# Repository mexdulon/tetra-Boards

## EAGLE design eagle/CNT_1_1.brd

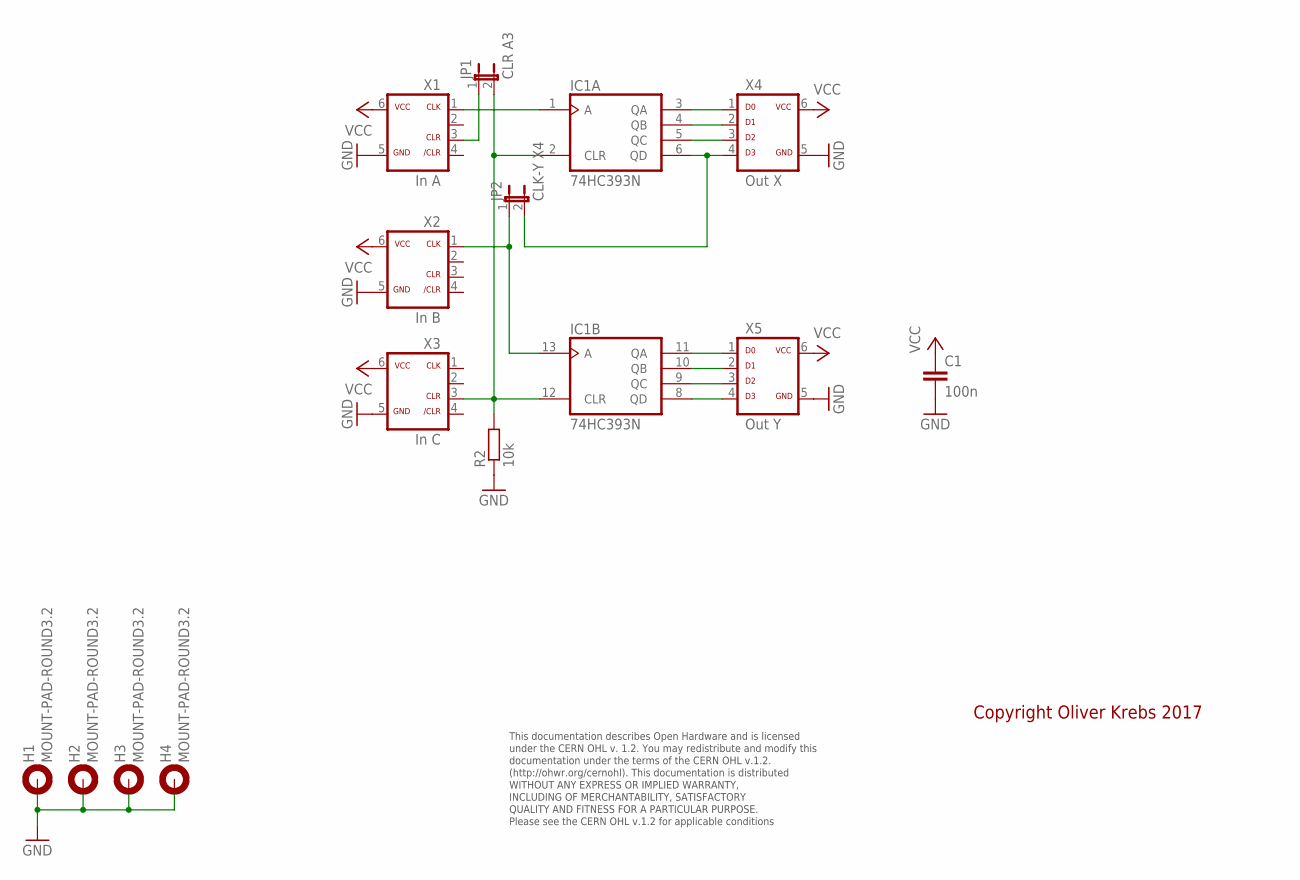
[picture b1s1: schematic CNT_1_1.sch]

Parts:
C1: 100n; C050-025X075
H1, H2, H3, H4: MOUNT-PAD-ROUND3.2; 3,2-PAD
IC1: 74HC393N; DIL14
JP1: CLR A3; JP1
JP2: CLK-Y X4; JP1
R2: 10k; 0207/10
X1: In A; ML-6
X2: In B; ML-6
X3: In C; ML-6
X4: Out X; ML-6
X5: Out Y; ML-6

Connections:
GND: C1.2, H1.B3,2, H2.B3,2, H3.B3,2, H4.B3,2, IC1.7 (GND), R2.1, X1.5, X2.5, X3.5, X4.5, X5.5
unnamed: IC1.3 (QA), X4.1
unnamed: IC1.4 (QB), X4.2
unnamed: IC1.5 (QC), X4.3
unnamed: IC1.1 (A), X1.1
unnamed: JP1.1, X1.3
unnamed: IC1.6 (QD), JP2.2, X4.4
unnamed: IC1.2 (CLR), IC1.12 (CLR), JP1.2, R2.2, X3.3
unnamed: IC1.13 (A), JP2.1, X2.1
unnamed: IC1.11 (QA), X5.1
unnamed: IC1.10 (QB), X5.2
unnamed: IC1.9 (QC), X5.3
unnamed: IC1.8 (QD), X5.4
VCC: C1.1, IC1.14 (VCC), X1.6, X2.6, X3.6, X4.6, X5.6

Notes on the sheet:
This documentation describes Open Hardware and is licensed under the CERN OHL v. 1.2. You may redistribute and modify this documentation under the terms of the CERN OHL v.1.2. (http://ohwr.org/cernohl). This documentation is distributed WITHOUT ANY EXPRESS OR IMPLIED WARRANTY, INCLUDING OF MERCHANT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
Copyright Oliver Krebs 2017

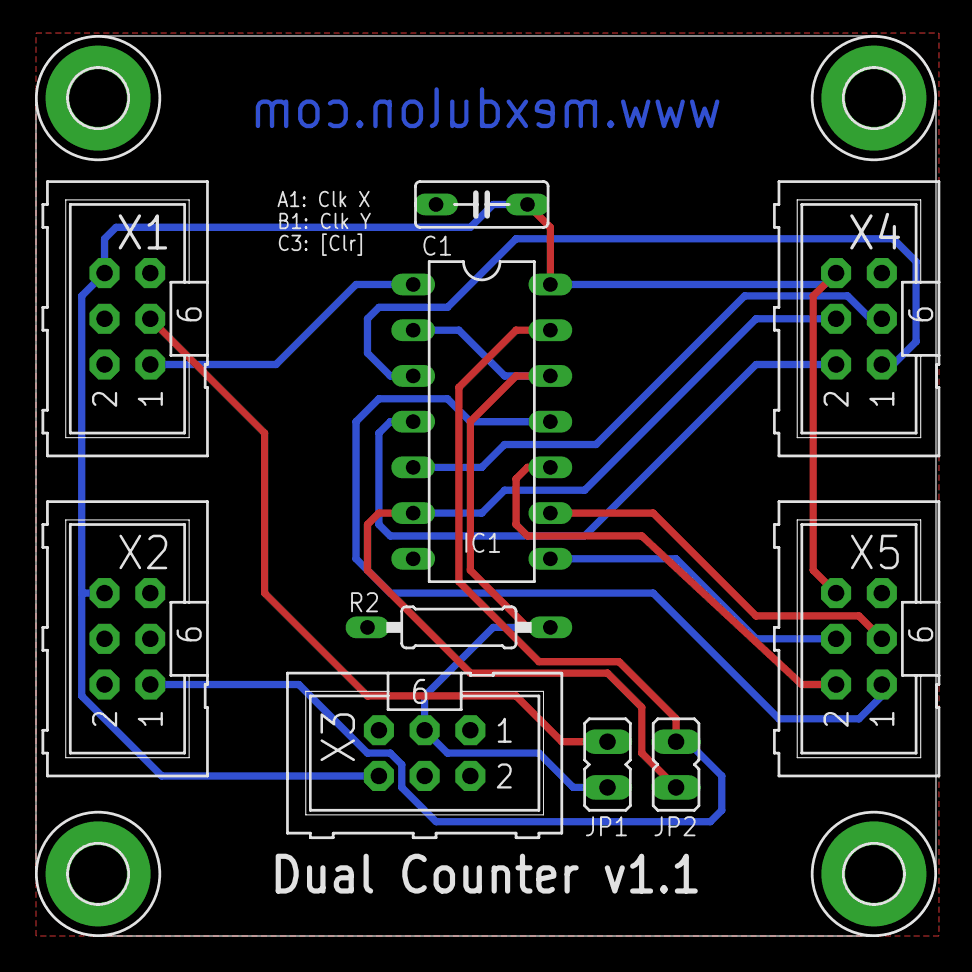
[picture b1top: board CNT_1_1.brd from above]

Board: 2 copper layers, 50.0 x 50.0 mm, 14 parts (0 on the bottom side), 14 nets.

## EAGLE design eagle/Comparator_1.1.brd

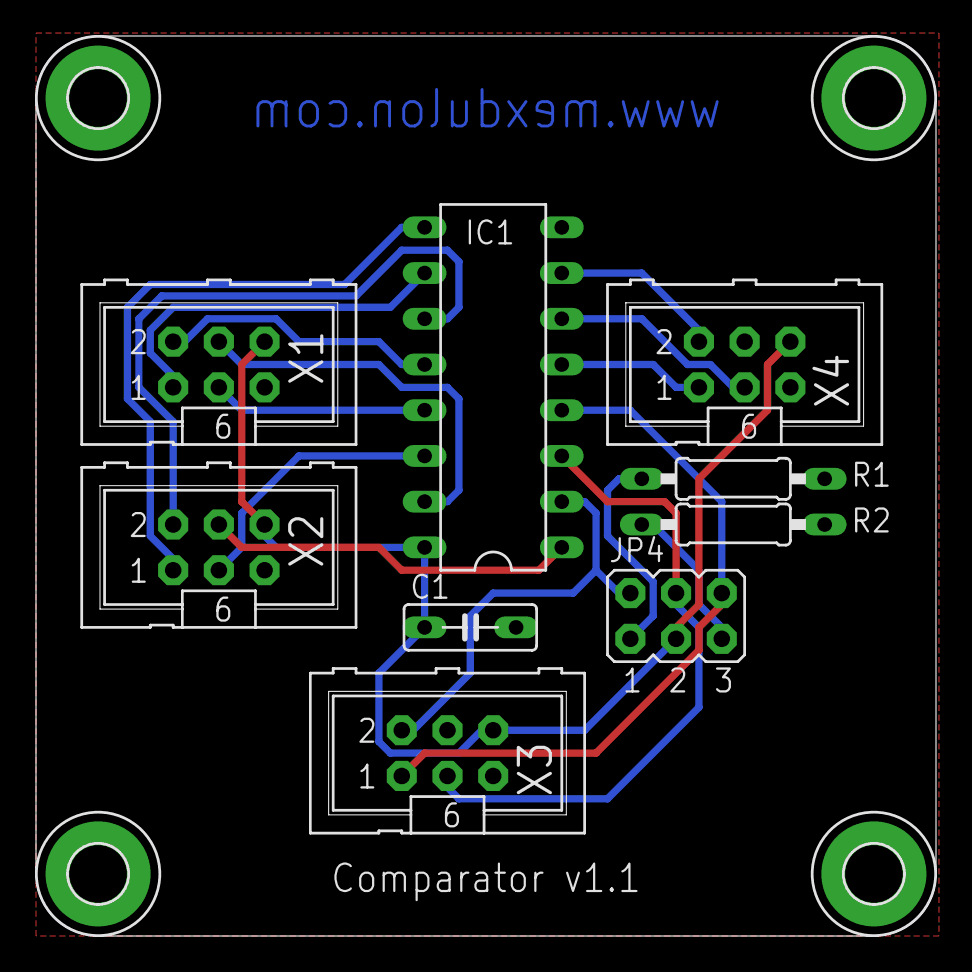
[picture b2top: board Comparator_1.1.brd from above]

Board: 2 copper layers, 50.0 x 50.0 mm, 13 parts (0 on the bottom side), 18 nets.

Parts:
C1: 100n; C050-025X075
H1, H2, H3, H4: MOUNT-PAD-ROUND3.2; 3,2-PAD
IC1: 74HC85N; DIL16
JP4: CMP STD; JP3Q
R1, R2: 10k; 0207/10
X1: In A; ML-6
X2: In B; ML-6
X3: In Cmp; ML-6
X4: Out; ML-6

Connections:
GND: C1.2, H1.B3,2, H2.B3,2, H3.B3,2, H4.B3,2, IC1.8, R1.2, R2.2, X1.5, X2.5, X3.5, X4.5
unnamed: IC1.10, X1.1
unnamed: IC1.12, X1.2
unnamed: IC1.13, X1.3
unnamed: IC1.15, X1.4
unnamed: IC1.9, X2.1
unnamed: IC1.11, X2.2
unnamed: IC1.14, X2.3
unnamed: IC1.1, X2.4
unnamed: IC1.3, JP4.4, X3.3
unnamed: IC1.2, JP4.2, X3.2
unnamed: IC1.4, JP4.6, X3.1
unnamed: IC1.5, X4.1
unnamed: IC1.7, X4.2
unnamed: IC1.6, X4.3
unnamed: JP4.1, R1.1
unnamed: JP4.5, R2.1
VCC: C1.1, IC1.16, JP4.3, X1.6, X2.6, X3.6, X4.6

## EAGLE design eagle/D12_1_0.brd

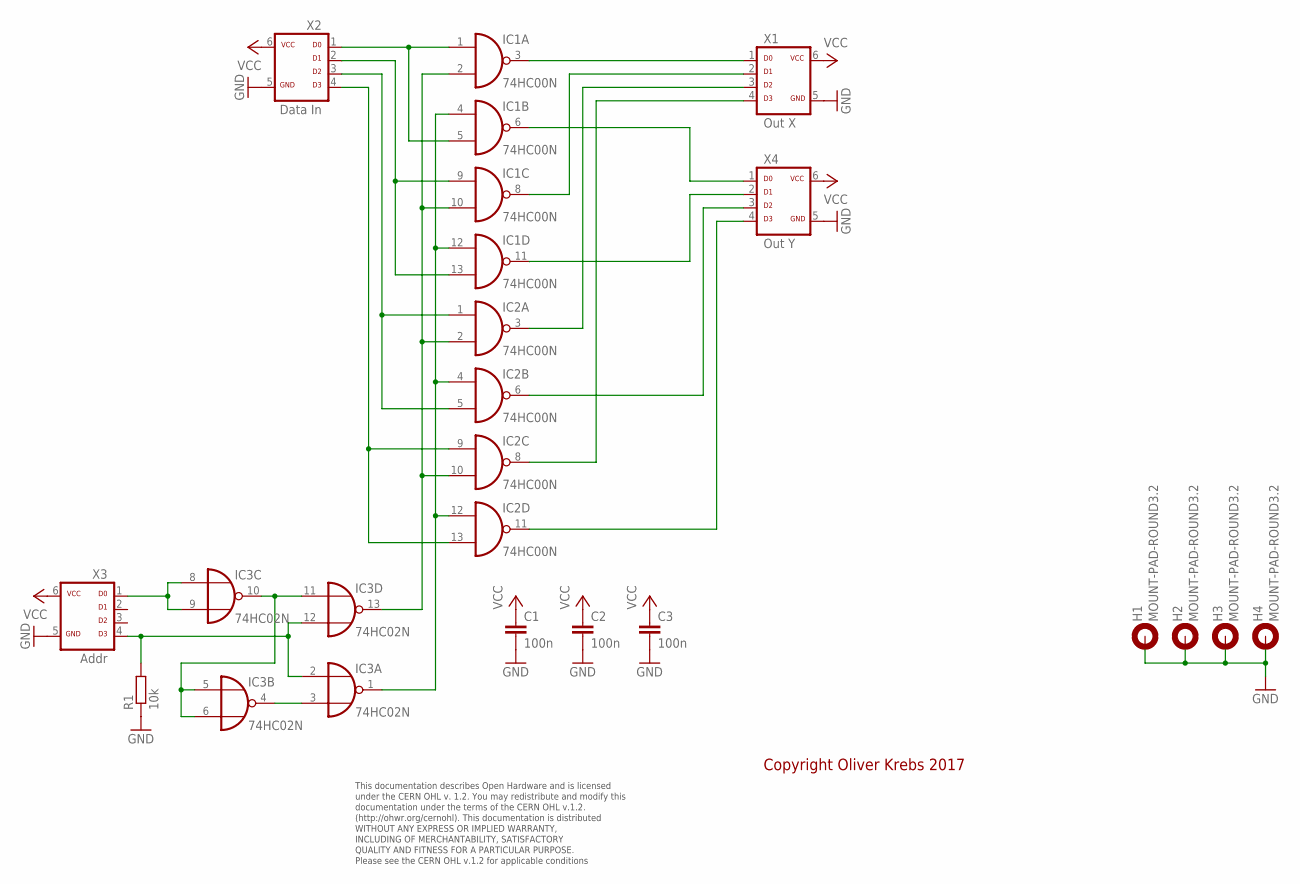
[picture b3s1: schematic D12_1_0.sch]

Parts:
C1, C2, C3: 100n; C050-025X075
H1, H2, H3, H4: MOUNT-PAD-ROUND3.2; 3,2-PAD
IC1, IC2: 74HC00N; DIL14
IC3: 74HC02N; DIL14
R1: 10k; 0207/10
X1: Out X; ML-6
X2: Data In; ML-6
X3: Addr; ML-6
X4: Out Y; ML-6

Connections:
GND: C1.2, C2.2, C3.2, H1.B3,2, H2.B3,2, H3.B3,2, H4.B3,2, IC1.7 (GND), IC2.7 (GND), IC3.7 (GND), R1.1, X1.5, X2.5, X3.5, X4.5
unnamed: IC1.3 (O), X1.1
unnamed: IC1.8 (O), X1.2
unnamed: IC2.3 (O), X1.3
unnamed: IC1.1 (I0), IC1.5 (I1), X2.1
unnamed: IC1.9 (I0), IC1.13 (I1), X2.2
unnamed: IC2.1 (I0), IC2.5 (I1), X2.3
unnamed: IC2.9 (I0), IC2.13 (I1), X2.4
unnamed: IC2.8 (O), X1.4
unnamed: IC1.6 (O), X4.1
unnamed: IC1.11 (O), X4.2
unnamed: IC2.6 (O), X4.3
unnamed: IC2.11 (O), X4.4
unnamed: IC3.5 (I0), IC3.6 (I1), IC3.10 (O), IC3.11 (I0)
unnamed: IC3.2 (I0), IC3.12 (I1), R1.2, X3.4
unnamed: IC1.2 (I1), IC1.10 (I1), IC2.2 (I1), IC2.10 (I1), IC3.13 (O)
unnamed: IC1.4 (I0), IC1.12 (I0), IC2.4 (I0), IC2.12 (I0), IC3.1 (O)
unnamed: IC3.3 (I1), IC3.4 (O)
unnamed: IC3.8 (I0), IC3.9 (I1), X3.1
VCC: C1.1, C2.1, C3.1, IC1.14 (VCC), IC2.14 (VCC), IC3.14 (VCC), X1.6, X2.6, X3.6, X4.6

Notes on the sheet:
This documentation describes Open Hardware and is licensed under the CERN OHL v. 1.2. You may redistribute and modify this documentation under the terms of the CERN OHL v.1.2. (http://ohwr.org/cernohl). This documentation is distributed WITHOUT ANY EXPRESS OR IMPLIED WARRANTY, INCLUDING OF MERCHANT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
Copyright Oliver Krebs 2017

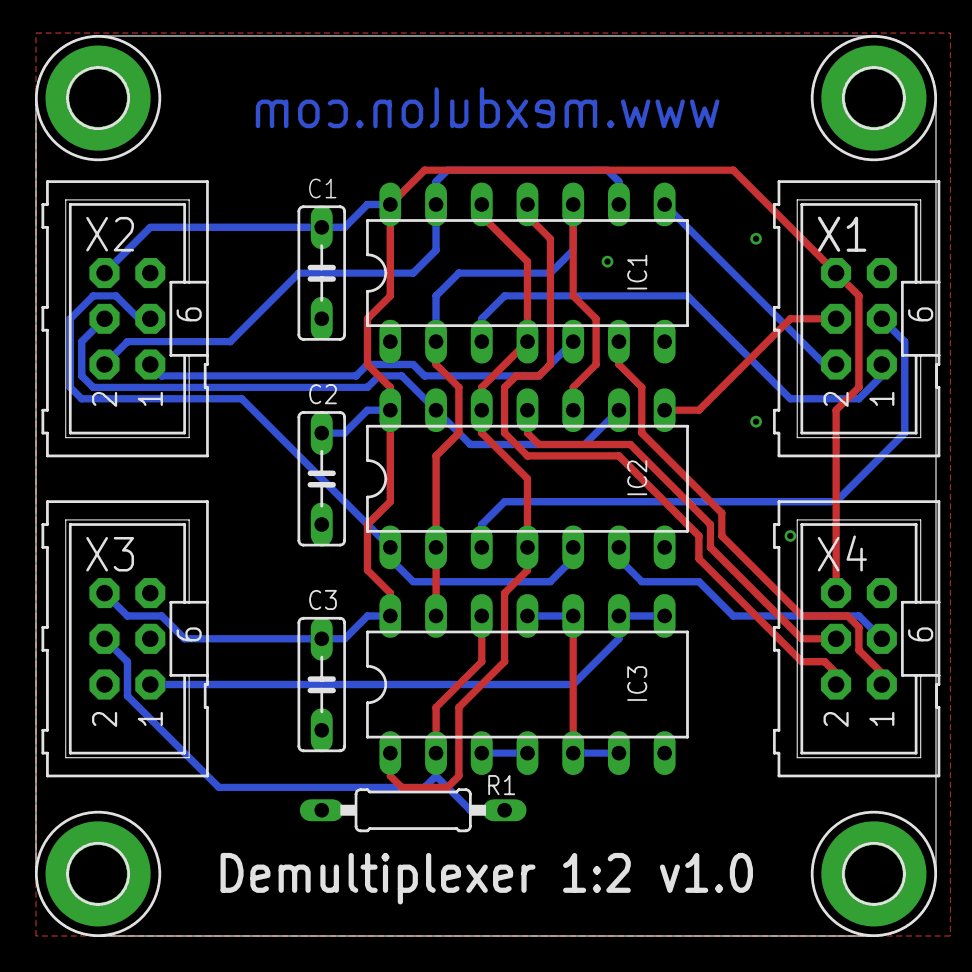
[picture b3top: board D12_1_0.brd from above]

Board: 2 copper layers, 50.0 x 50.0 mm, 15 parts (0 on the bottom side), 20 nets.

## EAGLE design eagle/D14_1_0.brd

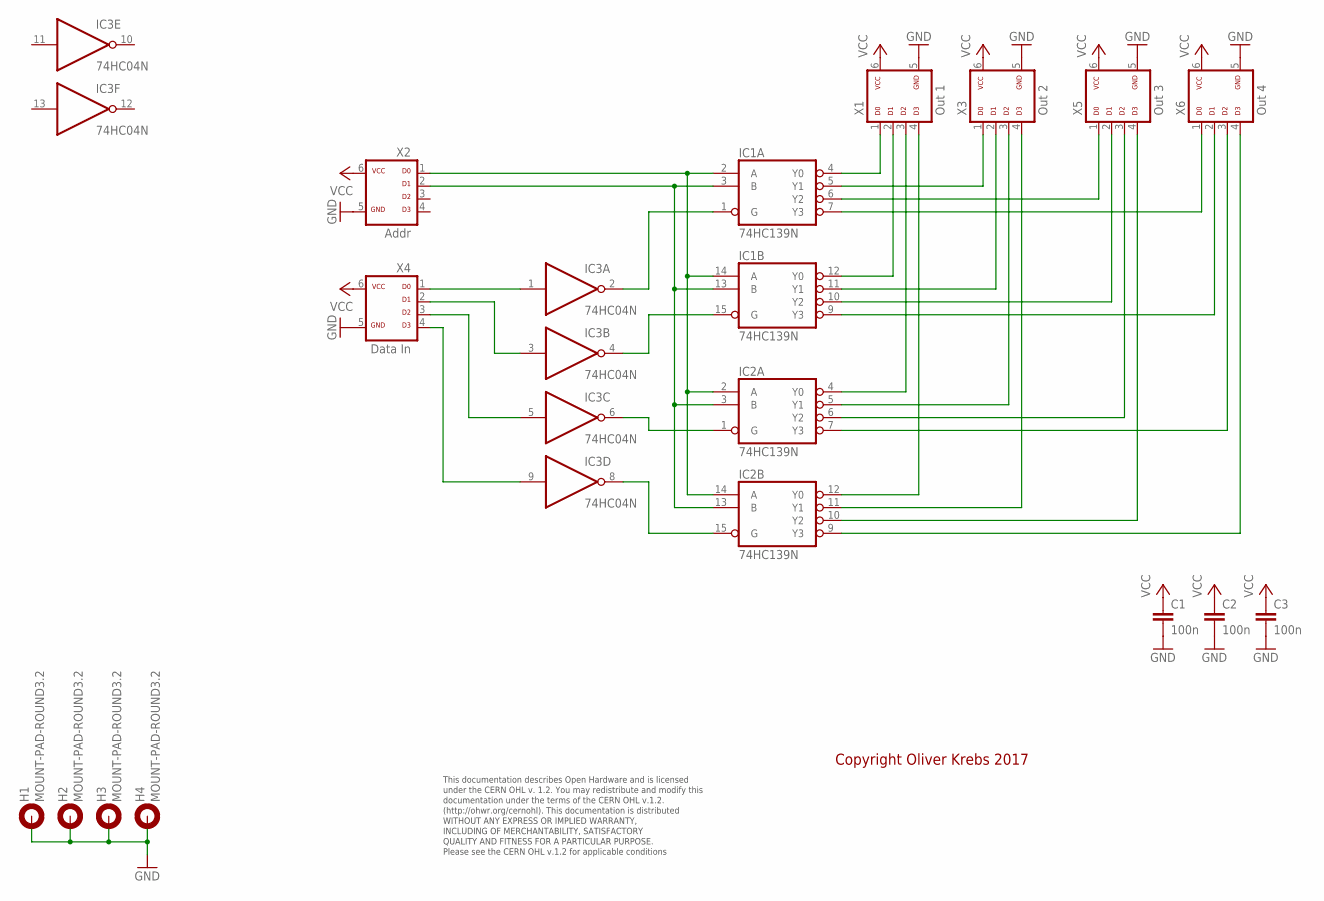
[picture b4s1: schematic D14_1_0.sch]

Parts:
C1, C2, C3: 100n; C050-025X075
H1, H2, H3, H4: MOUNT-PAD-ROUND3.2; 3,2-PAD
IC1, IC2: 74HC139N; DIL16
IC3: 74HC04N; DIL14
X1: Out 1; ML-6
X2: Addr; ML-6
X3: Out 2; ML-6
X4: Data In; ML-6
X5: Out 3; ML-6
X6: Out 4; ML-6

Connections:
GND: C1.2, C2.2, C3.2, H1.B3,2, H2.B3,2, H3.B3,2, H4.B3,2, IC1.8 (GND), IC2.8 (GND), IC3.7 (GND), X1.5, X2.5, X3.5, X4.5, X5.5, X6.5
unnamed: IC1.2 (A), IC1.14 (A), IC2.2 (A), IC2.14 (A), X2.1
unnamed: IC1.3 (B), IC1.13 (B), IC2.3 (B), IC2.13 (B), X2.2
unnamed: IC1.4 (Y0), X1.1
unnamed: IC1.12 (Y0), X1.2
unnamed: IC2.4 (Y0), X1.3
unnamed: IC2.12 (Y0), X1.4
unnamed: IC1.5 (Y1), X3.1
unnamed: IC1.11 (Y1), X3.2
unnamed: IC2.5 (Y1), X3.3
unnamed: IC2.11 (Y1), X3.4
unnamed: IC1.6 (Y2), X5.1
unnamed: IC1.10 (Y2), X5.2
unnamed: IC2.6 (Y2), X5.3
unnamed: IC2.10 (Y2), X5.4
unnamed: IC1.7 (Y3), X6.1
unnamed: IC1.9 (Y3), X6.2
unnamed: IC2.7 (Y3), X6.3
unnamed: IC2.9 (Y3), X6.4
unnamed: IC1.1 (G), IC3.2 (O)
unnamed: IC1.15 (G), IC3.4 (O)
unnamed: IC2.1 (G), IC3.6 (O)
unnamed: IC2.15 (G), IC3.8 (O)
unnamed: IC3.1 (I), X4.1
unnamed: IC3.3 (I), X4.2
unnamed: IC3.5 (I), X4.3
unnamed: IC3.9 (I), X4.4
VCC: C1.1, C2.1, C3.1, IC1.16 (VCC), IC2.16 (VCC), IC3.14 (VCC), X1.6, X2.6, X3.6, X4.6, X5.6, X6.6

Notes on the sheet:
This documentation describes Open Hardware and is licensed under the CERN OHL v. 1.2. You may redistribute and modify this documentation under the terms of the CERN OHL v.1.2. (http://ohwr.org/cernohl). This documentation is distributed WITHOUT ANY EXPRESS OR IMPLIED WARRANTY, INCLUDING OF MERCHANT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
Copyright Oliver Krebs 2017

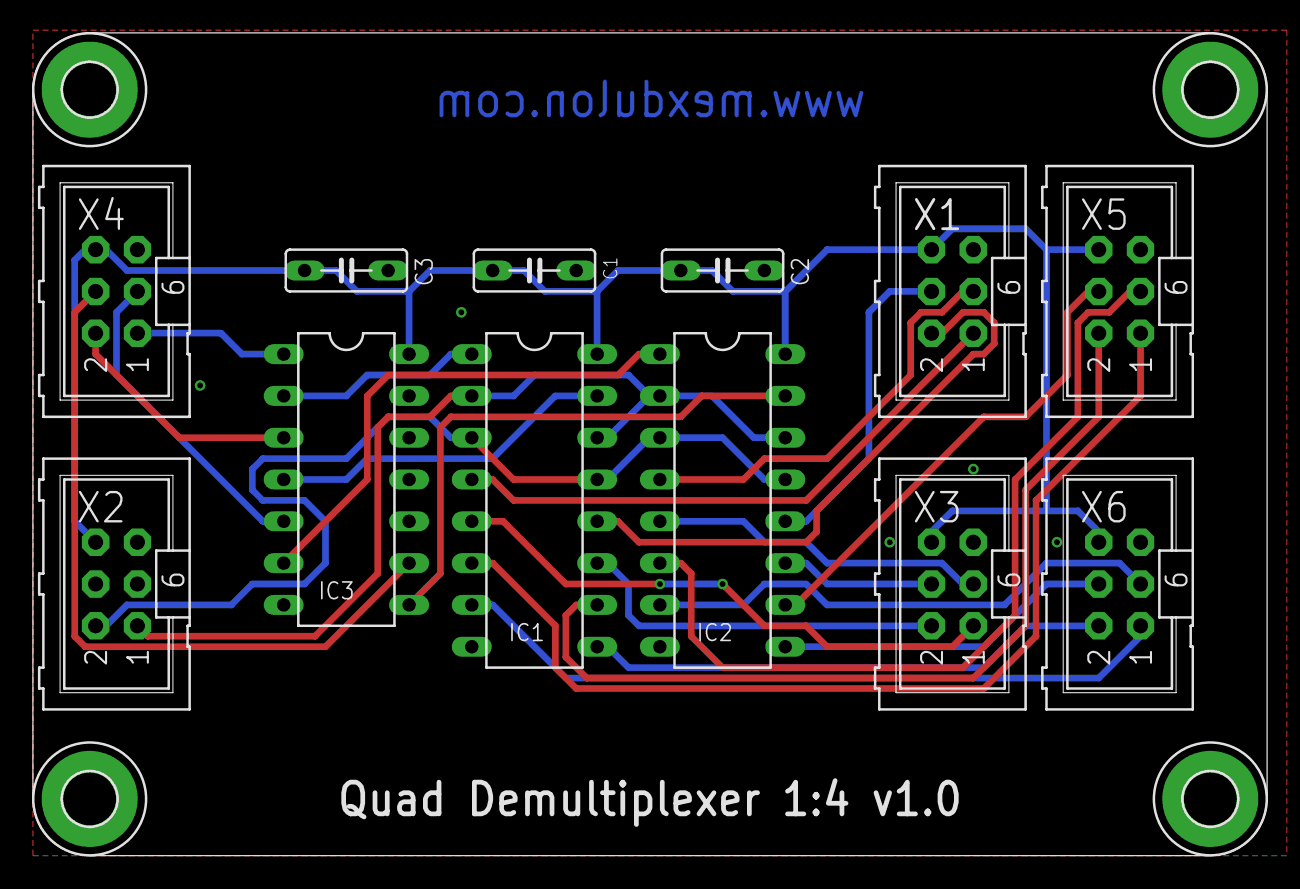
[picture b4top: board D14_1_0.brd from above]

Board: 2 copper layers, 75.0 x 50.0 mm, 16 parts (0 on the bottom side), 28 nets.

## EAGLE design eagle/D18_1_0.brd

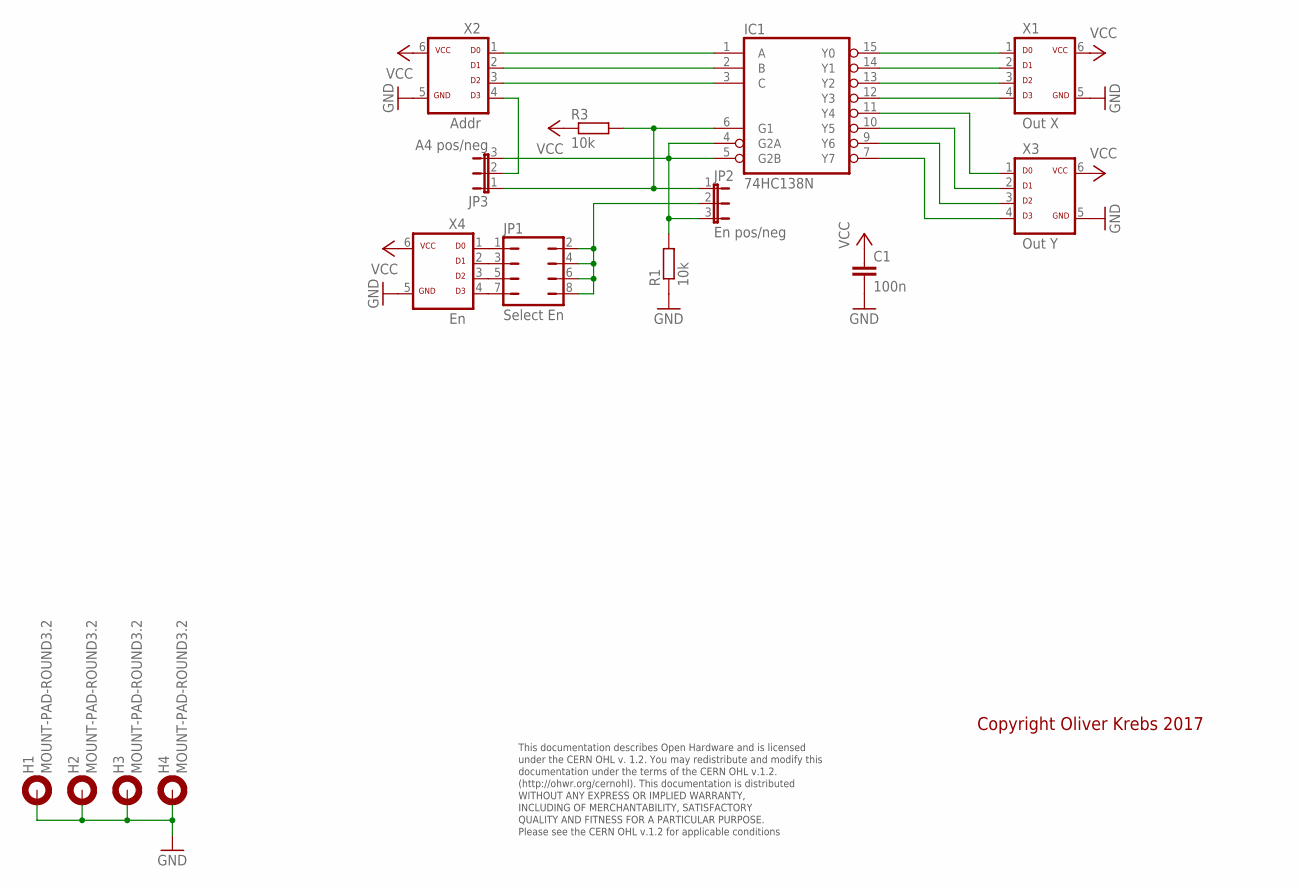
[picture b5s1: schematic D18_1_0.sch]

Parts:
C1: 100n; C050-025X075
H1, H2, H3, H4: MOUNT-PAD-ROUND3.2; 3,2-PAD
IC1: 74HC138N; DIL16
JP1: Select En; JP4Q
JP2: En pos/neg; JP2-U
JP3: A4 pos/neg; JP2-U
R1, R3: 10k; 0207/10
X1: Out X; ML-6
X2: Addr; ML-6
X3: Out Y; ML-6
X4: En; ML-6

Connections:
GND: C1.2, H1.B3,2, H2.B3,2, H3.B3,2, H4.B3,2, IC1.8 (GND), R1.1, X1.5, X2.5, X3.5, X4.5
unnamed: IC1.1 (A), X2.1
unnamed: IC1.2 (B), X2.2
unnamed: IC1.3 (C), X2.3
unnamed: JP3.2, X2.4
unnamed: JP1.2, JP1.4, JP1.6, JP1.8, JP2.2
unnamed: JP1.1, X4.1
unnamed: JP1.3, X4.2
unnamed: JP1.5, X4.3
unnamed: JP1.7, X4.4
unnamed: IC1.15 (Y0), X1.1
unnamed: IC1.14 (Y1), X1.2
unnamed: IC1.13 (Y2), X1.3
unnamed: IC1.12 (Y3), X1.4
unnamed: IC1.11 (Y4), X3.1
unnamed: IC1.10 (Y5), X3.2
unnamed: IC1.9 (Y6), X3.3
unnamed: IC1.7 (Y7), X3.4
unnamed: IC1.4 (G2A), IC1.5 (G2B), JP2.3, JP3.3, R1.2
unnamed: IC1.6 (G1), JP2.1, JP3.1, R3.2
VCC: C1.1, IC1.16 (VCC), R3.1, X1.6, X2.6, X3.6, X4.6

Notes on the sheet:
This documentation describes Open Hardware and is licensed under the CERN OHL v. 1.2. You may redistribute and modify this documentation under the terms of the CERN OHL v.1.2. (http://ohwr.org/cernohl). This documentation is distributed WITHOUT ANY EXPRESS OR IMPLIED WARRANTY, INCLUDING OF MERCHANT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
Copyright Oliver Krebs 2017

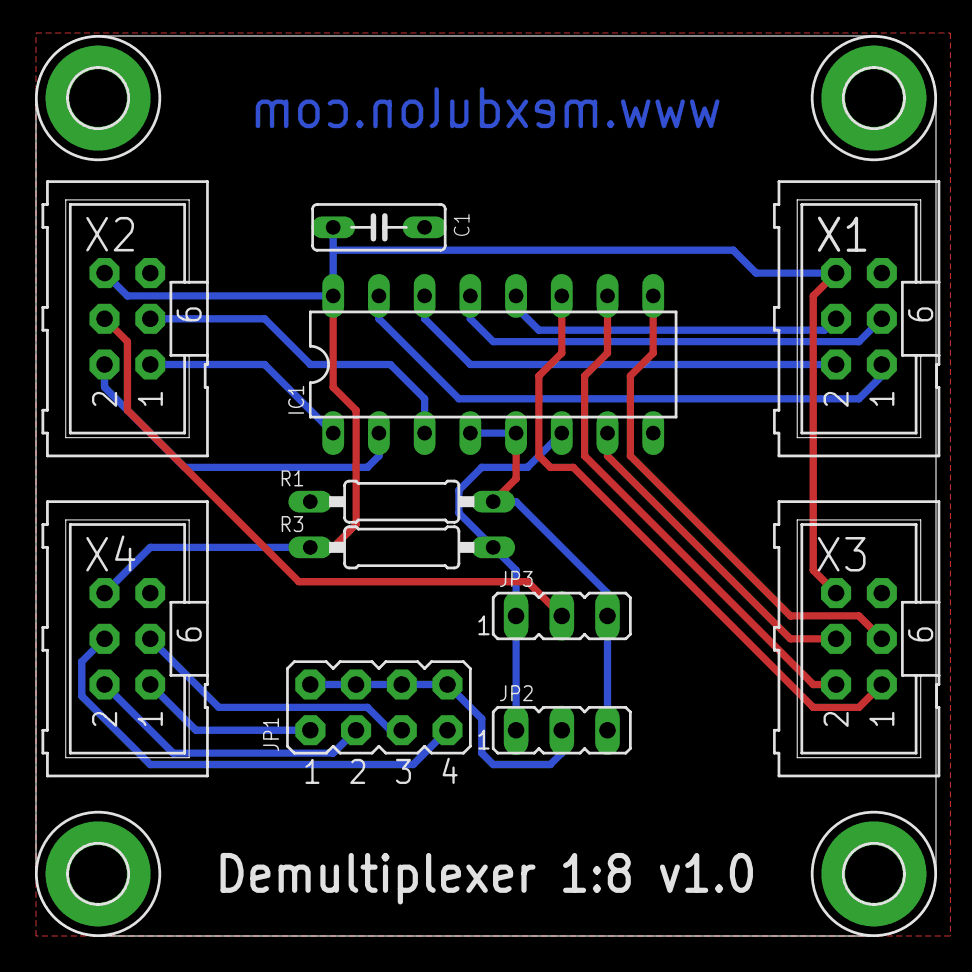
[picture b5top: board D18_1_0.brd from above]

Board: 2 copper layers, 50.0 x 50.0 mm, 15 parts (0 on the bottom side), 21 nets.

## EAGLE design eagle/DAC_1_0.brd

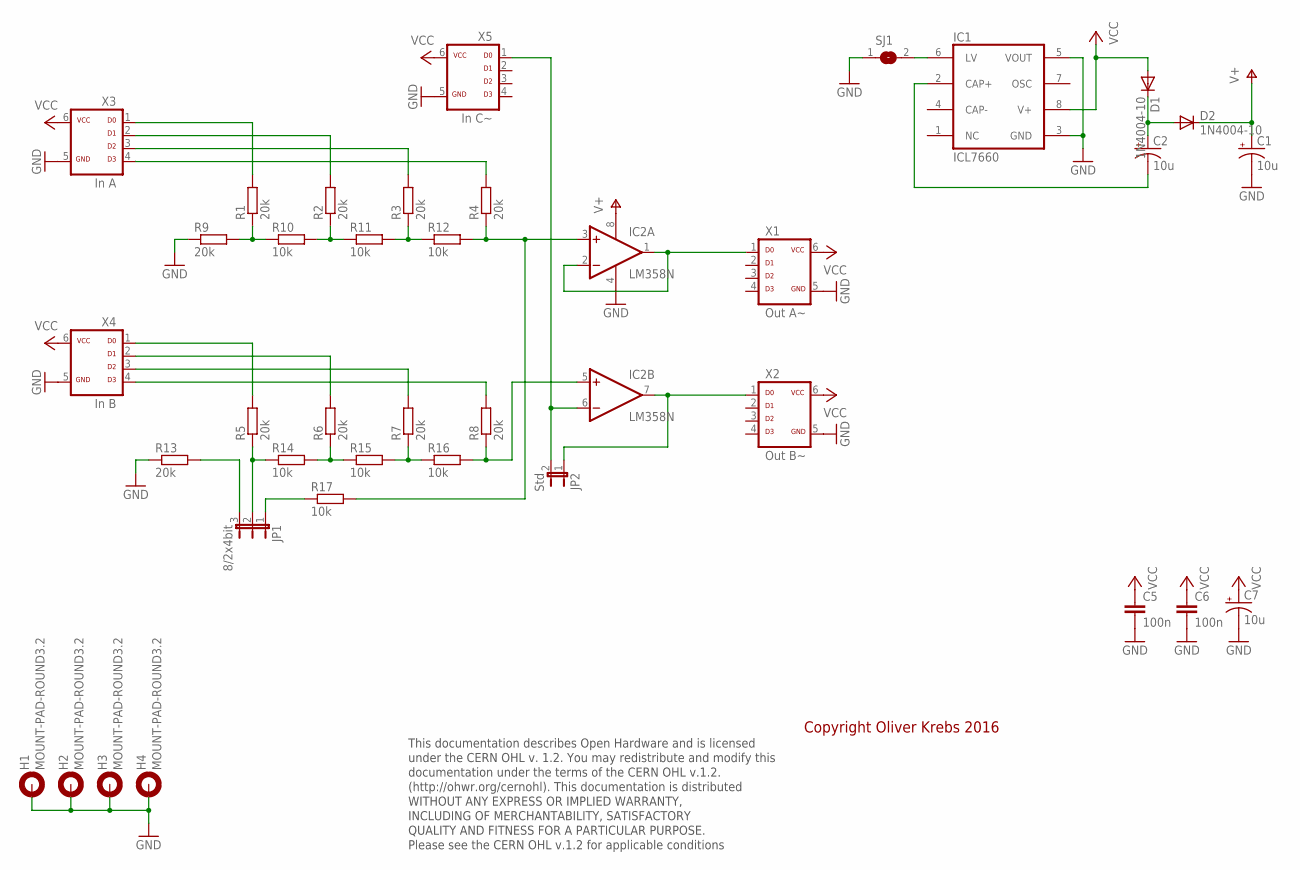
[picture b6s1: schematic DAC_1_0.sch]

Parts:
C1, C2, C7: 10u; CPOL-RADIAL-10UF-25V
C5, C6: 100n; CAP-PTH-5MM
D1, D2: 1N4004-10; DO41-10
H1, H2, H3, H4: MOUNT-PAD-ROUND3.2; 3,2-PAD
IC1: ICL7660; DIL08
IC2: LM358N; DIL08
JP1: 8/2x4bit; JP2-U
JP2: Std; JP1
R1, R2, R3, R4, R5, R6, R7, R8, R9, R13: 20k; 0207/2V
R10, R11, R12, R14, R15, R16, R17: 10k; 0207/2V
SJ1: SJ
X1: Out A~; ML-6
X2: Out B~; ML-6
X3: In A; ML-6
X4: In B; ML-6
X5: In C~; ML-6

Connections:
GND: C1.2 (-), C5.2, C6.2, C7.2 (-), H1.B3,2, H2.B3,2, H3.B3,2, H4.B3,2, IC1.3 (GND), IC1.5 (VOUT), IC2.4 (V-), R9.1, R13.1, SJ1.1, X1.5, X2.5, X3.5, X4.5, X5.5
unnamed: R1.2, X3.1
unnamed: R2.2, X3.2
unnamed: R3.2, X3.3
unnamed: R4.2, X3.4
unnamed: C2.2 (-), IC1.2 (CAP+)
unnamed: C2.1 (+), D1.C, D2.A
unnamed: R1.1, R9.2, R10.1
unnamed: R2.1, R10.2, R11.1
unnamed: R3.1, R11.2, R12.1
unnamed: IC2.3 (+IN), R4.1, R12.2, R17.2
unnamed: R5.2, X4.1
unnamed: R6.2, X4.2
unnamed: R7.2, X4.3
unnamed: R8.2, X4.4
unnamed: JP1.2, R5.1, R14.1
unnamed: R6.1, R14.2, R15.1
unnamed: R7.1, R15.2, R16.1
unnamed: IC2.5 (+IN), R8.1, R16.2
unnamed: JP1.3, R13.2
unnamed: IC2.1 (OUT), IC2.2 (-IN), X1.1
unnamed: IC2.7 (OUT), JP2.1, X2.1
unnamed: JP1.1, R17.1
unnamed: IC1.6 (LV), SJ1.2
unnamed: IC2.6 (-IN), JP2.2, X5.1
V+: C1.1 (+), D2.C, IC2.8 (V+)
VCC: C5.1, C6.1, C7.1 (+), D1.A, IC1.8 (V+), X1.6, X2.6, X3.6, X4.6, X5.6

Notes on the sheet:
This documentation describes Open Hardware and is licensed under the CERN OHL v. 1.2. You may redistribute and modify this documentation under the terms of the CERN OHL v.1.2. (http://ohwr.org/cernohl). This documentation is distributed WITHOUT ANY EXPRESS OR IMPLIED WARRANTY, INCLUDING OF MERCHANT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
Copyright Oliver Krebs 2016

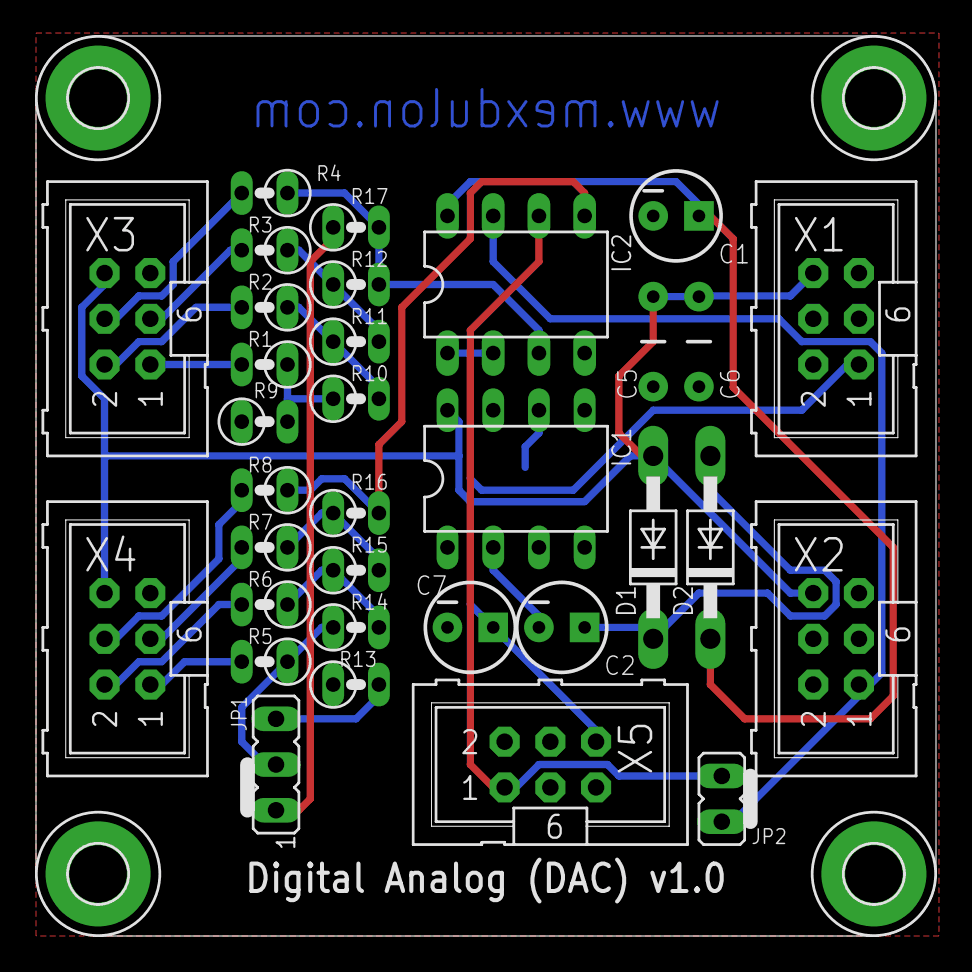
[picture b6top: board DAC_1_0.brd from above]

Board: 2 copper layers, 50.0 x 50.0 mm, 38 parts (1 on the bottom side), 27 nets.

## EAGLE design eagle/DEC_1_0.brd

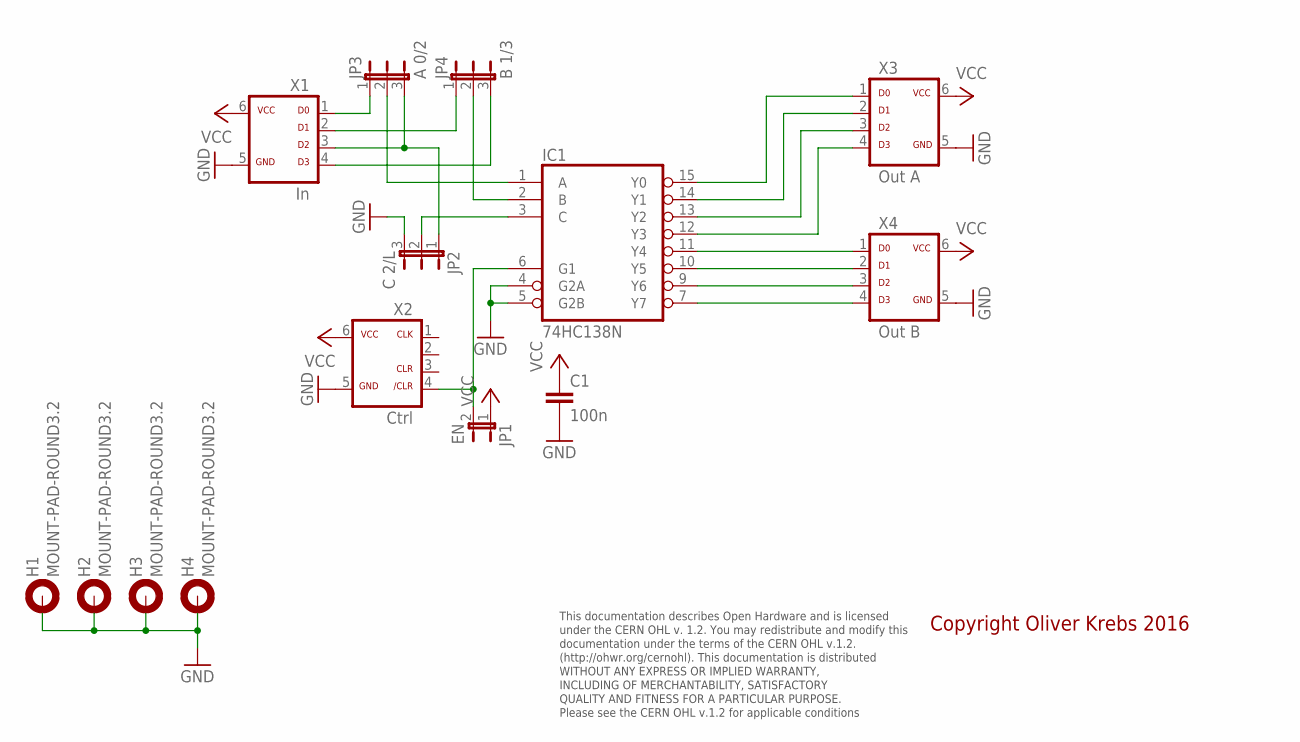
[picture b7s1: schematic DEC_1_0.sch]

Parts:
C1: 100n; C050-025X075
H1, H2, H3, H4: MOUNT-PAD-ROUND3.2; 3,2-PAD
IC1: 74HC138N; DIL16
JP1: EN; JP1
JP2: C 2/L; JP2
JP3: A 0/2; JP2
JP4: B 1/3; JP2
X1: In; ML-6
X2: Ctrl; ML-6
X3: Out A; ML-6
X4: Out B; ML-6

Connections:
GND: C1.2, H1.B3,2, H2.B3,2, H3.B3,2, H4.B3,2, IC1.4 (G2A), IC1.5 (G2B), IC1.8 (GND), JP2.3, X1.5, X2.5, X3.5, X4.5
unnamed: IC1.1 (A), JP3.2
unnamed: IC1.2 (B), JP4.2
unnamed: IC1.3 (C), JP2.2
unnamed: IC1.15 (Y0), X3.1
unnamed: IC1.14 (Y1), X3.2
unnamed: IC1.13 (Y2), X3.3
unnamed: IC1.12 (Y3), X3.4
unnamed: IC1.11 (Y4), X4.1
unnamed: IC1.10 (Y5), X4.2
unnamed: IC1.9 (Y6), X4.3
unnamed: IC1.7 (Y7), X4.4
unnamed: IC1.6 (G1), JP1.2, X2.4
unnamed: JP2.1, JP3.3, X1.3
unnamed: JP3.1, X1.1
unnamed: JP4.1, X1.2
unnamed: JP4.3, X1.4
VCC: C1.1, IC1.16 (VCC), JP1.1, X1.6, X2.6, X3.6, X4.6

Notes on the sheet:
This documentation describes Open Hardware and is licensed under the CERN OHL v. 1.2. You may redistribute and modify this documentation under the terms of the CERN OHL v.1.2. (http://ohwr.org/cernohl). This documentation is distributed WITHOUT ANY EXPRESS OR IMPLIED WARRANTY, INCLUDING OF MERCHANT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
Copyright Oliver Krebs 2016

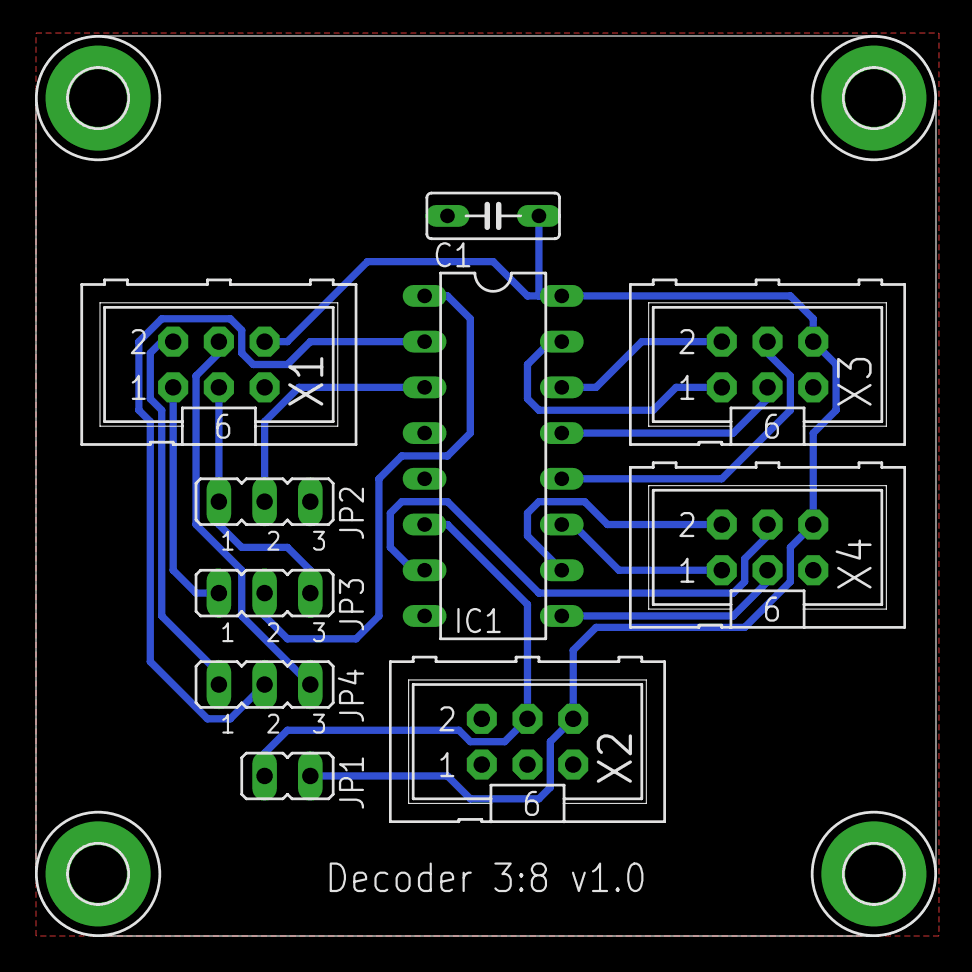
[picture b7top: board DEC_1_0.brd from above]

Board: 2 copper layers, 50.0 x 50.0 mm, 14 parts (0 on the bottom side), 18 nets.

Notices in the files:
eagle/CNT_1_1.brd:
Licensed under CERN OHL v.1.2
parts and their libraries:
SparkFun-Passives: Licensing: Creative Commons ShareAlike 4.0 International - https://creativecommons.org/licenses/by-sa/4.0
